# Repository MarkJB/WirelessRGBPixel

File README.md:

Copyright 2016 Mark Benson.

License: CC-NC-BY 4.0

No warranty implied or given. Use at your own risk.

Early testing code/electronics for proof of concept.

Wireless RGB Pixel is just that, a wireless (NRF24L01+) RGB led (WS2812b) controlled by an Atmel ATTiny85. One or more 'pixels' can be controlled by an Arduino with another NRF24L01+ module.

It is hoped that many of these 'pixels' can be manufactured and installed somewhere and controlled to create an interesting light show.

As of Dec 2016 PCB is at v1.2.

This version uses the original circuit design. No pin mux or serial debug is available.

More details on the Make Bournemouth Wiki and forum.

https://www.makebournemouth.com/wiki2/index.php/RGB_Wireless_Pixel

https://www.makebournemouth.com/?page_id=39

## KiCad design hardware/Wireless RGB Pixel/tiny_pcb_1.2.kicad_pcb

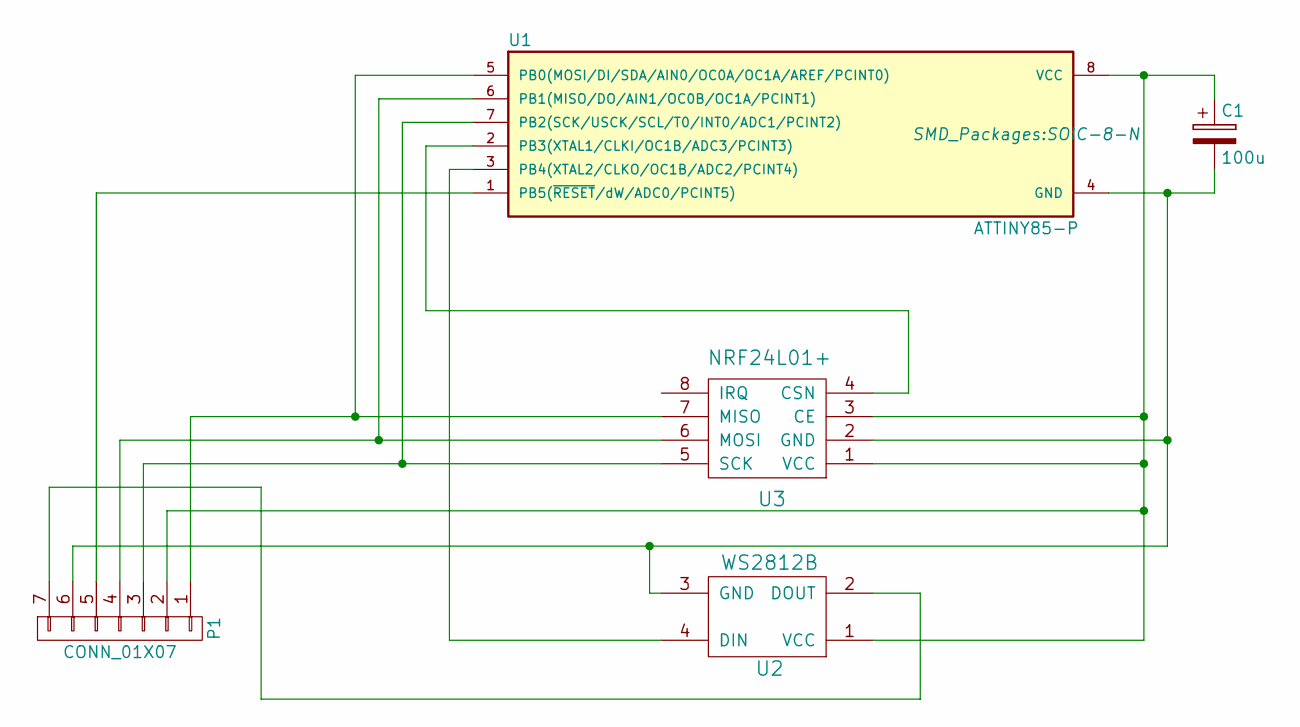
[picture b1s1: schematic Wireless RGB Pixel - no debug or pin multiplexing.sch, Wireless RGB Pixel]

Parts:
C1: 100u; TantalC_SizeB_EIA-3528_Reflow
P1: CONN_01X07; CONN7
U1: ATTINY85-P; SOIC-8-N
U2: WS2812B; WS2812B_SMT
U3: NRF24L01+; NRF24L01+_SMT

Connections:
unnamed: C1.1, P1.2, U1.8 (VCC), U2.1 (VCC), U3.1 (VCC), U3.3 (CE)
unnamed: C1.2, P1.6, U1.4 (GND), U2.3 (GND), U3.2 (GND)
unnamed: P1.1, U1.5 (PB0(MOSI/DI/SDA/AIN0/OC0A/OC1A/AREF/PCI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), U3.7 (MISO)
unnamed: P1.3, U1.7 (PB2(SCK/USCK/SCL/T0/INT0/ADC1/PCINT2)), U3.5 (SCK)
unnamed: P1.4, U1.6 (PB1(MISO/DO/AIN1/OC0B/OC1A/PCINT1)), U3.6 (MOSI)
unnamed: P1.5, U1.1 (PB5(~RESET~/dW/ADC0/PCINT5))
unnamed: P1.7, U2.2 (DOUT)
unnamed: U1.2 (PB3(XTAL1/CLKI/OC1B/ADC3/PCINT3)), U3.4 (CSN)
unnamed: U1.3 (PB4(XTAL2/CLKO/OC1B/ADC2/PCINT4)), U2.4 (DIN)

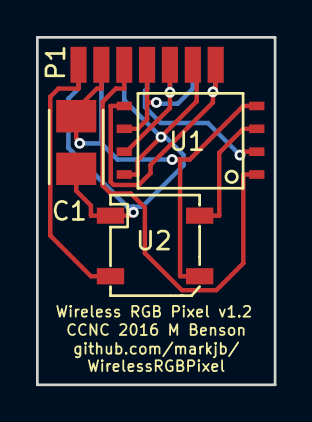
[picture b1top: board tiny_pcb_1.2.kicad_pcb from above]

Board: 2 copper layers, 13.2 x 19.3 mm, 5 parts (1 on the bottom side), 9 nets.

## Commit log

2016-07-11 :circus_tent: Added .gitattributes & .gitignore files
2016-07-11 Initial commit
    PoC schematic and test software (largely based on the RF24 getting
    started examples. To be replaced with proper working code.)
2016-07-11 Readme
2016-07-24 Serial control
2016-07-25 Testing pixel addressing
2016-08-29 Fix file extension and CE, CSN pin assignment
2016-12-27 v1.2, back to original design with no pin mux, no serial debug to simplify custom nrf lib
2016-12-27 Pic of assembled v1.2 pcb
2017-02-23 Updated schematic - no debug

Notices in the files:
hardware/Wireless RGB Pixel/Wireless RGB Pixel - no debug or pin multiplexing.sch:
Copyright Mark Benson 2016
License Creative Commons Atribution 4.0 (CC-BY 4.0)
